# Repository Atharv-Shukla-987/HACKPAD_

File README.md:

# L_PAD 

It is L shape micropad. It is my first project. Thanks to hack club, I got a chance to design it.I have always faced many problems in remembering the shortkeys , so i added my most used shortkeys. It's design is inspired from sandwich, its case has no wall which gives it fi look . It can be attached with keyboard as it is L shaped. It has 12 keys and some leds.

# SCHEMATIC_DESIGN

I have design this PCB using KiCAD. 
Here are some pictures.

# PCB_DESIGN

I also have make  holes with smooth out Conners so it won't wobble. 

# PCB_3D

It is 3d image of my PCB design.

# case_top

I have designed the case using fussion 360 . The design is consist of just two plates top and bottom plate. Here is image of top plate.

# case_bottom

Here is image of top plate.

# case

Here is image of both top and bottom plate assemble.

# L_PAD

here is image of whole micropad or L_PAD.

# FIRMWARE OVERVEIW

I have use KMK for my firmware.These are the keys which will on my L_PAD.

Row 1: Essentials (2 Keys)

​Key 1: Copy (Ctrl + C)
​Key 2: Paste (Ctrl + V)
​Row 2: VS Code Navigation (2 Keys)
​Key 3: Command Palette (Ctrl + Shift + P)
​Key 4: Quick Open File (Ctrl + P)

​Row 3: ML - Google Colab (4 Keys)

​Key 5: Run Cell and Move (Shift + Enter)
​Key 6: Run All Above (Ctrl + F9)
​Key 7: New Code Cell (Ctrl + M then B)
​Key 8: Interrupt Execution (Ctrl + M then I)

Row 4: Power User Navigation (4 Keys)

​Key 9: Task View (Win + Tab)
​Key 10: Clipboard History (Win + V)
​Key 11: Reopen Closed Tab (Ctrl + Shift + T)
​Key 12: Quick Switcher (Alt + Tab)

# BOM

Here should be everything you need to make this hackpad

    12x Cherry MX Switches
    12x DSA Keycaps
    4x M3x16 Bolt
    12x SK6812 MINI Leds
    12x 1N4148 DO-35 Diodes.
    1x XIAO RP2040
    1x Case (top_plate and bottom_plate)

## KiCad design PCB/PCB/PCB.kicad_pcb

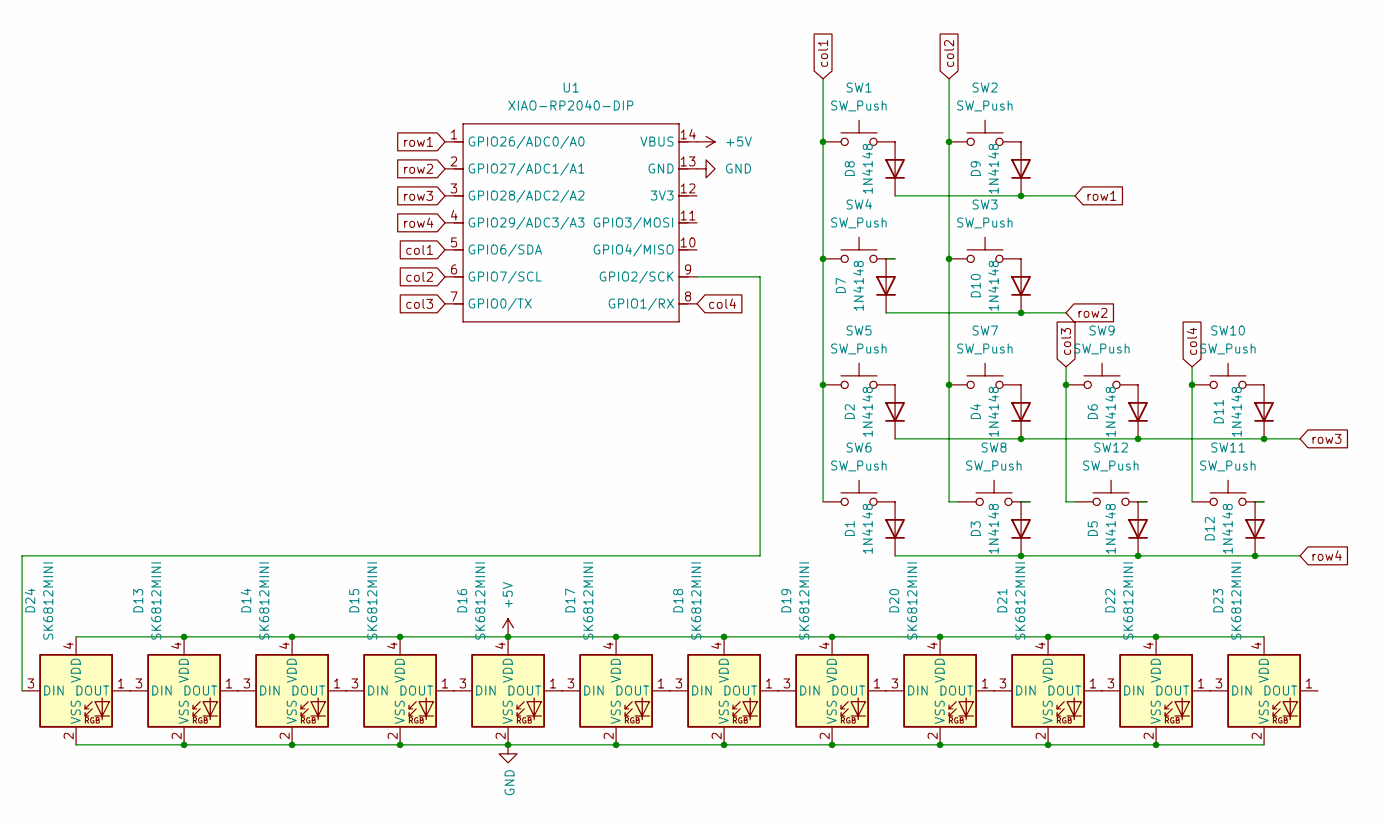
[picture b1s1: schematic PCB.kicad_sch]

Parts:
D1, D2, D3, D4, D5, D6, D7, D8, D9, D10, D11, D12: 1N4148; D_DO-35_SOD27_P7.62mm_Horizontal
D13, D14, D15, D16, D17, D18, D19, D20, D21, D22, D23, D24: SK6812MINI; LED_SK6812MINI_PLCC4_3.5x3.5mm_P1.75mm
SW1, SW2, SW3, SW4, SW5, SW6, SW7, SW8, SW9, SW10, SW11, SW12: SW_Push; SW_Cherry_MX_1.00u_PCB
U1: XIAO-RP2040-DIP

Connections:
+5V: D13.4 (VDD), D14.4 (VDD), D15.4 (VDD), D16.4 (VDD), D17.4 (VDD), D18.4 (VDD), D19.4 (VDD), D20.4 (VDD), D21.4 (VDD), D22.4 (VDD), D23.4 (VDD), D24.4 (VDD), U1.14 (VBUS)
GND: D13.2 (VSS), D14.2 (VSS), D15.2 (VSS), D16.2 (VSS), D17.2 (VSS), D18.2 (VSS), D19.2 (VSS), D20.2 (VSS), D21.2 (VSS), D22.2 (VSS), D23.2 (VSS), D24.2 (VSS), U1.13 (GND)
unnamed: D1.2 (A), SW6.2
unnamed: D2.2 (A), SW5.2
unnamed: D3.2 (A), SW8.2
unnamed: D4.2 (A), SW7.2
unnamed: D5.2 (A), SW12.2
unnamed: D6.2 (A), SW9.2
unnamed: D7.2 (A), SW4.2
unnamed: D8.2 (A), SW1.2
unnamed: D9.2 (A), SW2.2
unnamed: D10.2 (A), SW3.2
unnamed: D11.2 (A), SW10.2
unnamed: D12.2 (A), SW11.2
unnamed: D13.3 (DIN), D24.1 (DOUT)
unnamed: D13.1 (DOUT), D14.3 (DIN)
unnamed: D14.1 (DOUT), D15.3 (DIN)
unnamed: D15.1 (DOUT), D16.3 (DIN)
unnamed: D16.1 (DOUT), D17.3 (DIN)
unnamed: D17.1 (DOUT), D18.3 (DIN)
unnamed: D18.1 (DOUT), D19.3 (DIN)
unnamed: D19.1 (DOUT), D20.3 (DIN)
unnamed: D20.1 (DOUT), D21.3 (DIN)
unnamed: D21.1 (DOUT), D22.3 (DIN)
unnamed: D22.1 (DOUT), D23.3 (DIN)
unnamed: D24.3 (DIN), U1.9 (GPIO2/SCK)
col1: SW1.1, SW4.1, SW5.1, SW6.1, U1.5 (GPIO6/SDA)
col2: SW2.1, SW3.1, SW7.1, SW8.1, U1.6 (GPIO7/SCL)
col3: SW9.1, SW12.1, U1.7 (GPIO0/TX)
col4: SW10.1, SW11.1, U1.8 (GPIO1/RX)
row1: D8.1 (K), D9.1 (K), U1.1 (GPIO26/ADC0/A0)
row2: D7.1 (K), D10.1 (K), U1.2 (GPIO27/ADC1/A1)
row3: D2.1 (K), D4.1 (K), D6.1 (K), D11.1 (K), U1.3 (GPIO28/ADC2/A2)
row4: D1.1 (K), D3.1 (K), D5.1 (K), D12.1 (K), U1.4 (GPIO29/ADC3/A3)

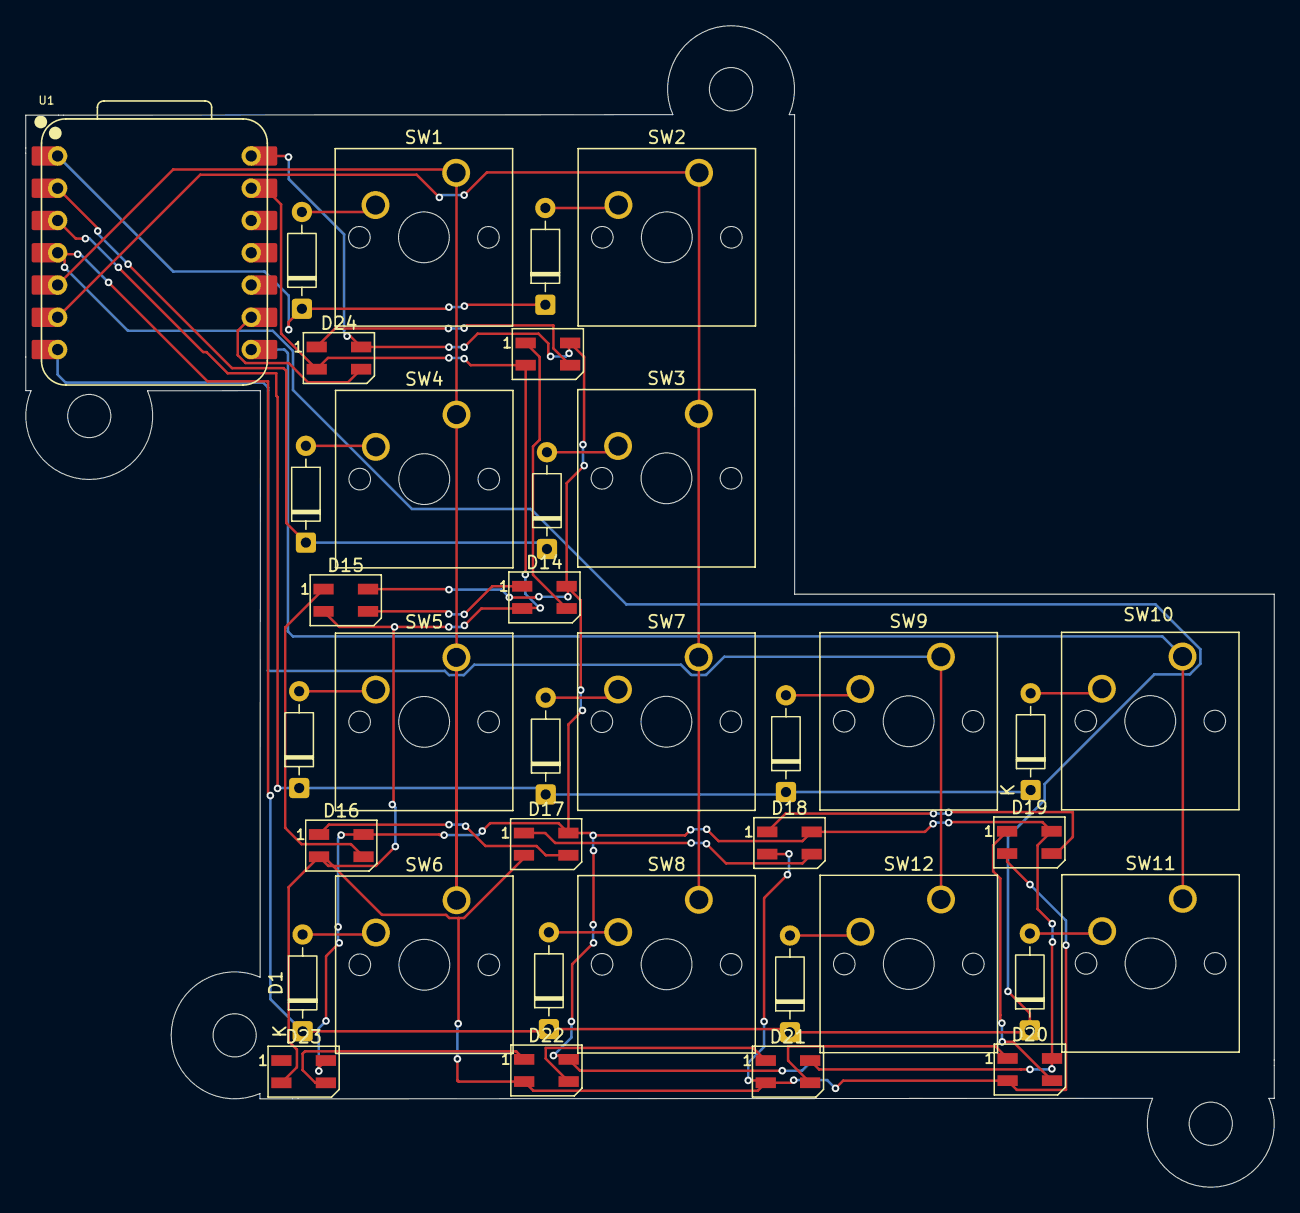
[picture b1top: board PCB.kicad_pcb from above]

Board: 2 copper layers, 98.3 x 91.4 mm, 37 parts (0 on the bottom side), 34 nets.

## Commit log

2026-01-31 Create firmware.main.py for keyboard configuration
    Initialized keyboard with pin mapping and shortcuts.
2026-01-31 Update README with design images and BOM
    Added schematic, PCB, and case design images along with BOM details.
2026-01-31 Update README with design images and BOM
    Added images and descriptions for schematic, PCB, and case designs.
2026-02-01 Add PCB design image to README
    Added a new PCB design image to the README.
2026-02-01 Add images for PCB design and case top
2026-02-01 Update README with PCB_DESIGN image placeholder
    Added a placeholder for PCB_DESIGN image upload.
2026-02-06 Enhance README with project details and firmware overview
    Updated the README to include additional details about the L_PAD project, including firmware overview and key mappings.
2026-02-06 Change L_PAD header from H1 to H3
    Updated the header level for L_PAD and made minor text adjustments.
2026-02-06 Fix heading formatting in README.md
    Updated headings in README.md for consistency and clarity.
2026-02-06 Enhance README with PCB and case design details
    Added descriptions and images for PCB and case designs.
2026-02-06 Enhance README with project images and details
    Added images and descriptions for various components of the L_PAD project, including schematic design, PCB design, and case assembly.
2026-02-06 Add images for case_bottom and L_PAD
    Added images for case_bottom and L_PAD sections in README.
